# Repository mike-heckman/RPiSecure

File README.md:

Welcome!

This board is designed to "glue" parts to a Raspberry Pi for an RFID door lock.

It attaches on top of the the Pi using the stacking header and uses an L293D
half-H motor driver and an MCP23017 digital IO expander so the other (optional)
components don't take up all the Raspbery Pi's GPIO pins.

If the board is fully populated, it provides the following:

   Two bi-directional motor drivers with either coupled or independent power.
   Connections for two switches, intended for door position (hall-effect sensor) and deadbolt position (tactile momentary switch depressed by the deadbolt).
   Connections for one or two DHT-22 temperature and humidity sensors.
   Connections for up to four LEDs (one is hardwired for power, the other three are on IO ports).
   A connection for a speaker.
   8 additional IO ports addressed through the MCP23017.

The board is designed to use the minimum number of pins on the Raspberry Pi.
To use the second motor driver you have to jumper the MTR2 pins, or tie them
to other pins on the Raspberry Pi breakout.

Also the INTB pins can be jumpered if you want interrupt access to the second
bank of GPIO on the MCP23017 - you don't have to unless you want the interrupt
to go to GPIO pin 4.

You also need to set three jumpers for the MCP23017 3 low id bits.

The board intentionally doesn't draw power from the Pi as it will be powered by
DC/DC power converters from a common 12v source.  There's a pin header near the
upper left corner that provides a +5V and GND power to optionally power the Pi.

The board should work for either the model B or B+ Raspberry Pis.

Datasheets are available for most parts:

L293D Motor Driver:  http://www.farnell.com/datasheets/1804890.pdf
MCP21037 Digital IO: http://www.farnell.com/datasheets/12179.pdf

Standard Traces are 10 mil with 12 mil isolation, the traces for the motor
power in out and to the L293D are larger as it can switch motors up to 36V.
The top and bottom ground planes have been maximized around the chips to allow
them to sink heat into the board.

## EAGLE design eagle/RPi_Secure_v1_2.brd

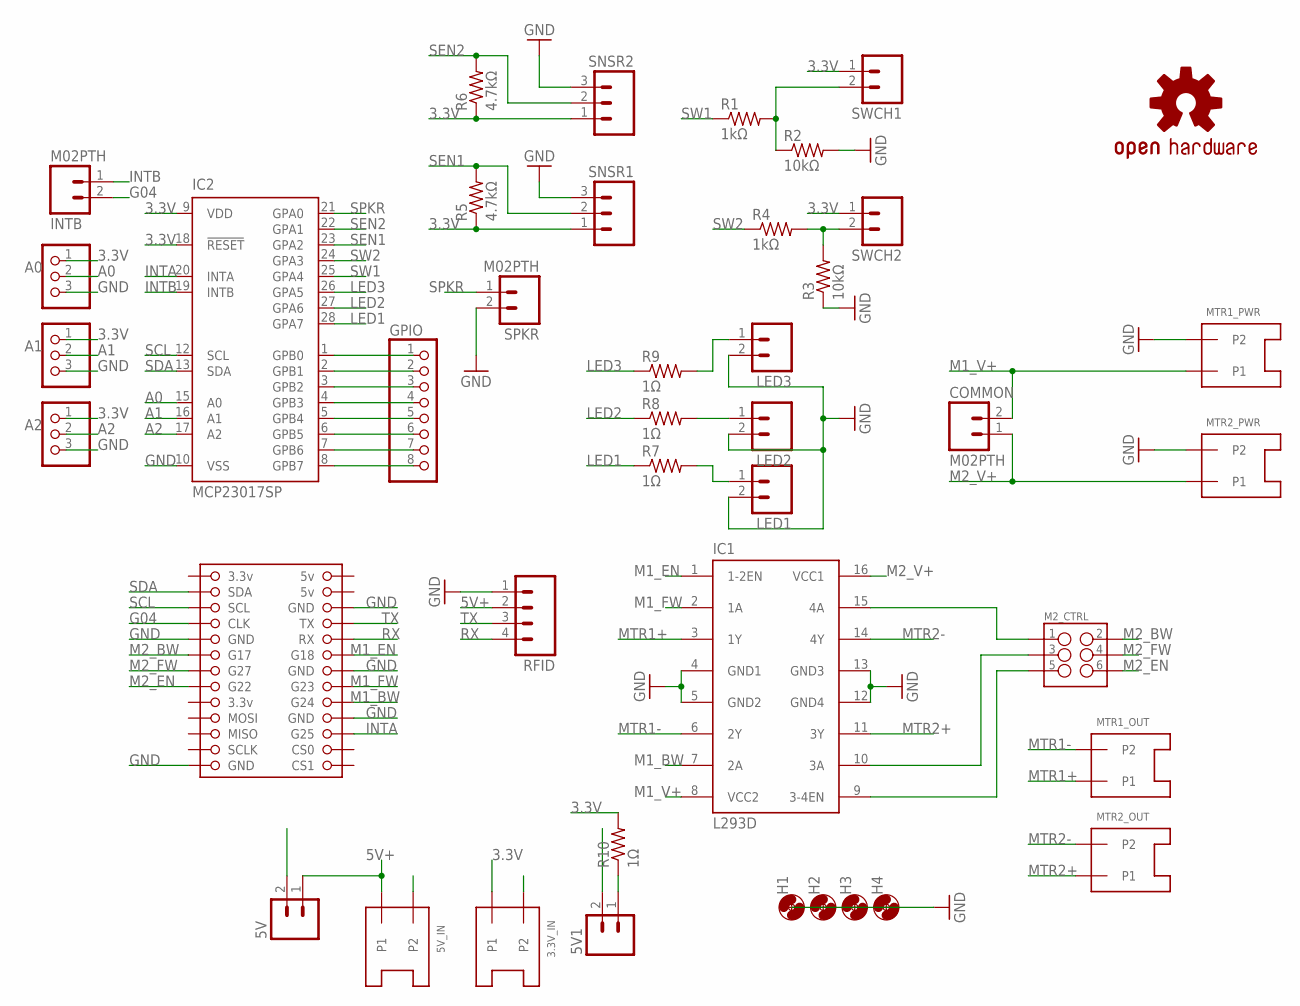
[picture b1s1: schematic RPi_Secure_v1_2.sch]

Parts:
3.3V_IN, 5V_IN: S2B-XH-AS2B-XH-A; S2B-XH-A
5V, 5V1: M02PTH; 1X02; MPN 22-28-4023
A0, A1, A2: PINHD-1X3; 1X03; MPN 22-28-4033
COMMON: M02PTH; 1X02; MPN 22-28-4023
GPIO: PINHD-1X8; 1X08; MPN 22-28-4080
H1, H2, H3, H4: MOUNT-HOLE2.8; 2,8
IC1: L293D; DIL16
IC2: MCP23017SP; DIL28-3; MPN MCP23017-E/SP
INTB: M02PTH; 1X02; MPN 22-28-4023
JP1: 1112RPI_EXTRA_LONG; 1112
LED1, LED2, LED3: M02PTH; 1X02; MPN 22-28-4023
LOGO2: OSHW-LOGOM; OSHW-LOGO-M
M2_CTRL: M03X22X3_SILK_SM; 2X3
MTR1_OUT, MTR1_PWR, MTR2_OUT, MTR2_PWR: S2B-XH-AS2B-XH-A; S2B-XH-A
R1, R4: 1kΩ; R0805
R2, R3: 10kΩ; R0805
R5, R6: 4.7kΩ; R0805
R7, R8, R9, R10: 1Ω; R0805
RFID: M04PTH; 1X04; MPN 22-28-4040
SNSR1, SNSR2: M03PTH; 1X03; MPN 22-28-4033
SPKR: M02PTH; 1X02; MPN 22-28-4023
SWCH1, SWCH2: M02PTH; 1X02; MPN 22-28-4023

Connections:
01: JP1.01
02: JP1.02
3.3V: 3.3V_IN.P1, A0.1, A1.1, A2.1, IC2.9 (VDD), IC2.18 (!RESET), R5.1, R6.1, R10.2, SNSR1.1, SNSR2.1, SWCH1.1, SWCH2.1
04: JP1.04
5V+: 5V.1, 5V_IN.P1, RFID.2
17: JP1.17
A0: A0.2, IC2.15 (A0)
A1: A1.2, IC2.16 (A1)
A2: A2.2, IC2.17 (A2)
G04: INTB.2, JP1.07
GND: 3.3V_IN.P2, 5V.2, 5V1.2, 5V_IN.P2, A0.3, A1.3, A2.3, IC1.4 (GND1), IC1.5 (GND2), IC1.12 (GND4), IC1.13 (GND3), IC2.10 (VSS), JP1.06, JP1.09, JP1.14, JP1.20, JP1.25, LED1.2, LED2.2, LED3.2, MTR1_PWR.P2, MTR2_PWR.P2, R2.2, R3.1, RFID.1, SNSR1.3, SNSR2.3, SPKR.2
INTA: IC2.20 (INTA), JP1.22
INTB: IC2.19 (INTB), INTB.1
LED1: IC2.28 (GPA7), R7.1
LED2: IC2.27 (GPA6), R8.1
LED3: IC2.26 (GPA5), R9.1
M1_BW: IC1.7 (2A), JP1.18
M1_EN: IC1.1 (1-2EN), JP1.12
M1_FW: IC1.2 (1A), JP1.16
M1_V+: COMMON.2, IC1.8 (VCC2), MTR1_PWR.P1
M2_BW: JP1.11, M2_CTRL.2
M2_EN: JP1.15, M2_CTRL.6
M2_FW: JP1.13, M2_CTRL.4
M2_V+: COMMON.1, IC1.16 (VCC1), MTR2_PWR.P1
MTR1+: IC1.3 (1Y), MTR1_OUT.P1
MTR1-: IC1.6 (2Y), MTR1_OUT.P2
MTR2+: IC1.11 (3Y), MTR2_OUT.P1
MTR2-: IC1.14 (4Y), MTR2_OUT.P2
unnamed: LED1.1, R7.2
unnamed: LED2.1, R8.2
unnamed: LED3.1, R9.2
unnamed: R3.2, R4.2, SWCH2.2
unnamed: 5V1.1, R10.1
unnamed: IC1.10 (3A), M2_CTRL.3
unnamed: IC1.15 (4A), M2_CTRL.1
unnamed: GPIO.1, IC2.1 (GPB0)
unnamed: GPIO.2, IC2.2 (GPB1)
unnamed: GPIO.3, IC2.3 (GPB2)
unnamed: GPIO.4, IC2.4 (GPB3)
unnamed: GPIO.5, IC2.5 (GPB4)
unnamed: GPIO.6, IC2.6 (GPB5)
unnamed: GPIO.7, IC2.7 (GPB6)
unnamed: GPIO.8, IC2.8 (GPB7)
RX: JP1.10, RFID.4
SCL: IC2.12 (SCL), JP1.05
SDA: IC2.13 (SDA), JP1.03
SEN1: IC2.23 (GPA2), R5.2, SNSR1.2
SEN2: IC2.22 (GPA1), R6.2, SNSR2.2
SPKR: IC2.21 (GPA0), SPKR.1
SW1: IC2.25 (GPA4), R1.1, R1.2, R2.1, SWCH1.2
SW2: IC2.24 (GPA3), R4.1
TX: JP1.08, RFID.3
X: IC1.9 (3-4EN), M2_CTRL.5

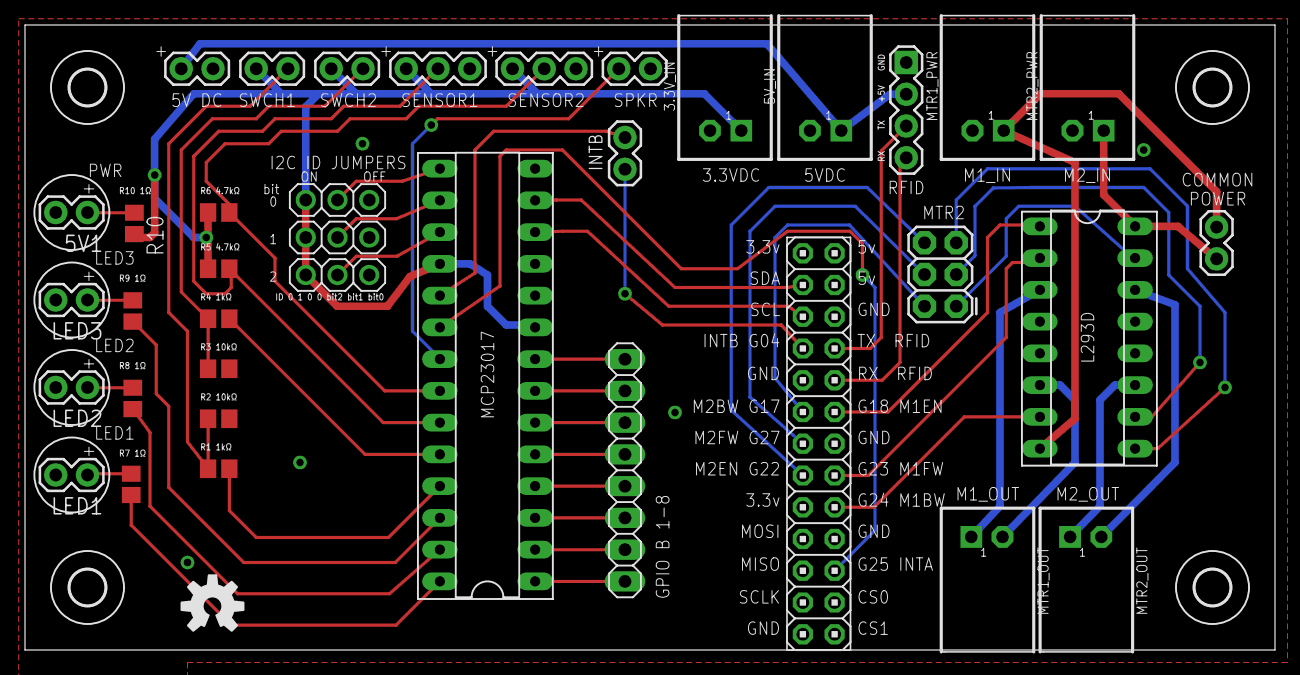
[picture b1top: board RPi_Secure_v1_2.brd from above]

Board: 4 copper layers, 100.0 x 50.0 mm, 42 parts (0 on the bottom side), 49 nets.

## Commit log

2014-08-18 Initial checkin

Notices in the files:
parts and their libraries:
SparkFun-Connectors: Licensing: Creative Commons ShareAlike 4.0 International - https://creativecommons.org/licenses/by-sa/4.0
